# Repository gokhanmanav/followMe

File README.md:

# followMe

This application was developed for special education students.

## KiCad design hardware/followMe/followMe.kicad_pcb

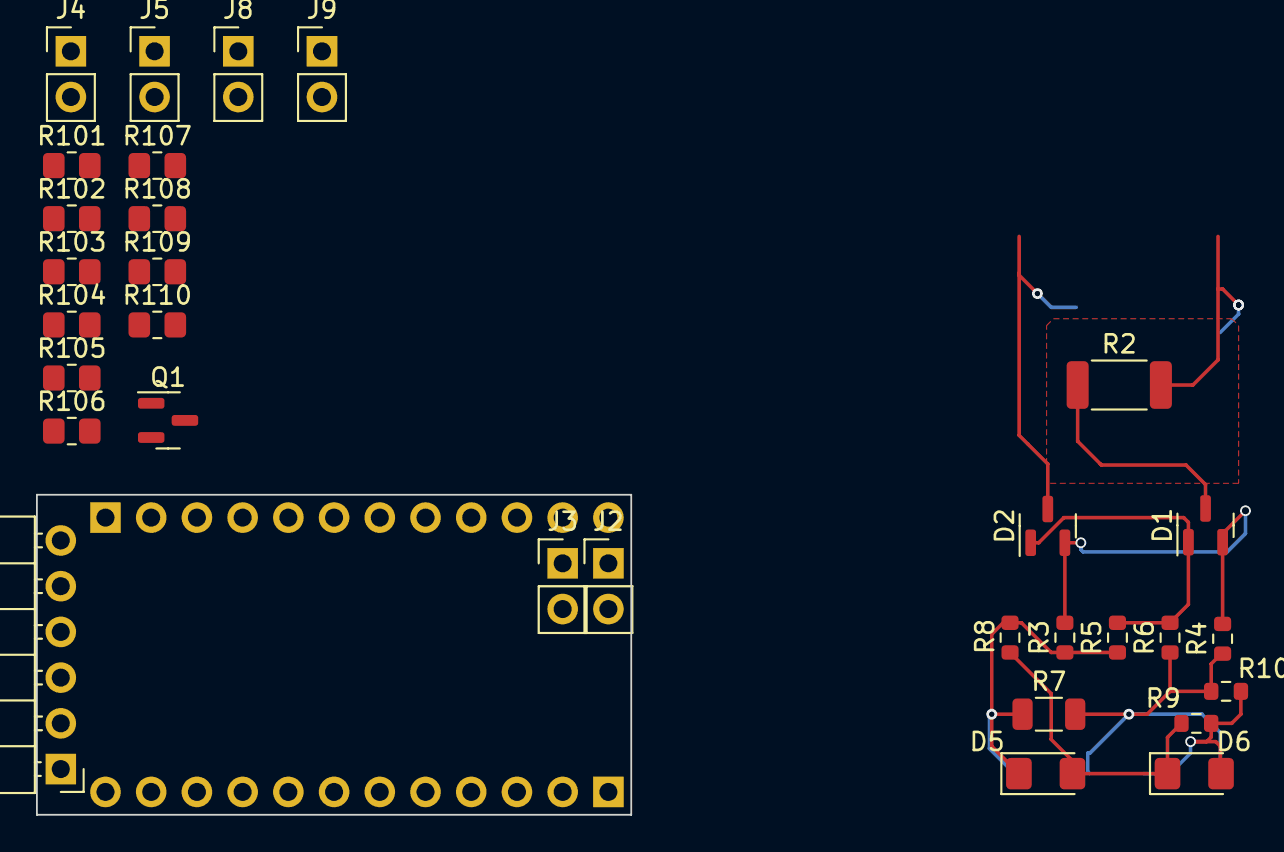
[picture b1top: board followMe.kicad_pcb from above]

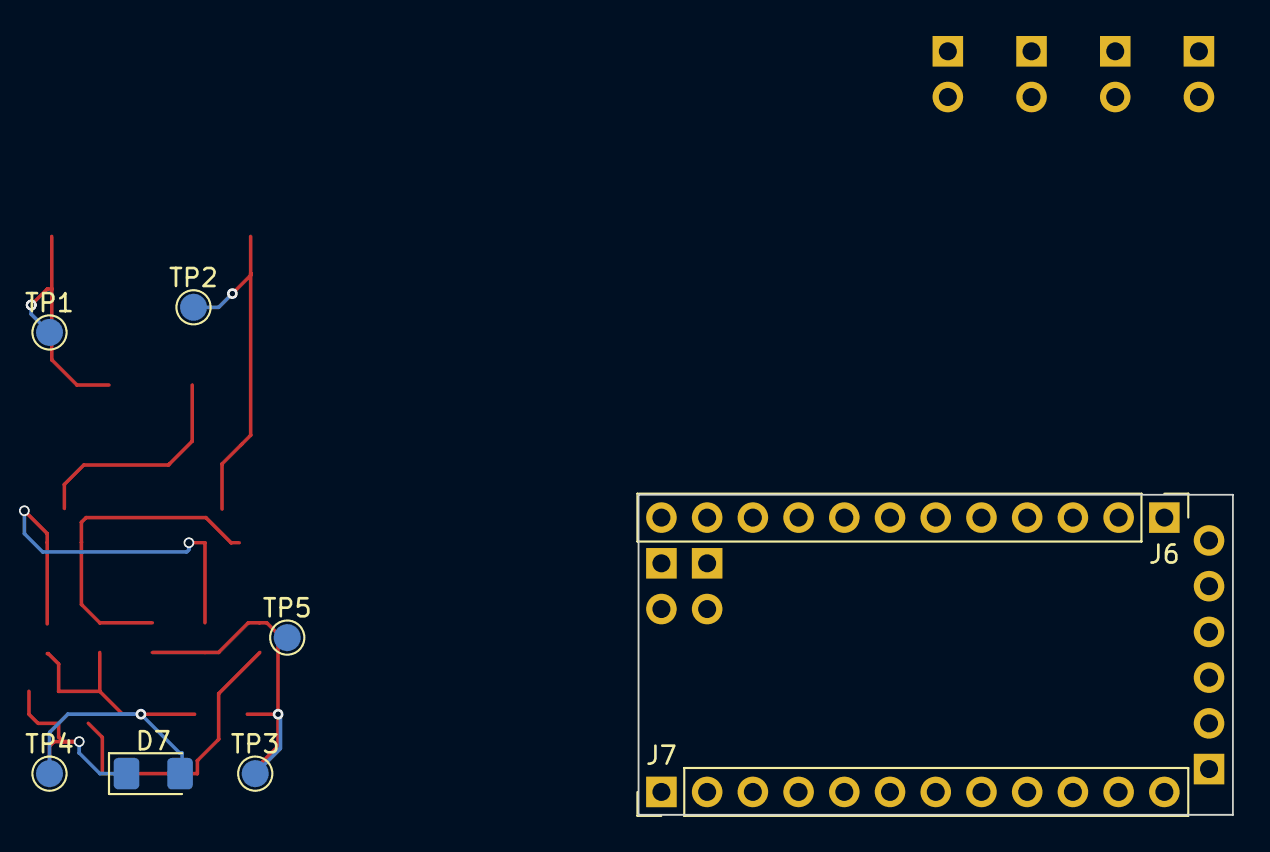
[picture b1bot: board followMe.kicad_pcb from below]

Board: 2 copper layers, 33.0 x 17.8 mm, 39 parts (8 on the bottom side), 26 nets.

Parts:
D1, D2: BAV99; SOT-23
D5, D6, D7: LED; LED_1206_3216Metric_Pad1.42x1.75mm_HandSolder
J1: FTDI; PinHeader_1x06_P2.54mm_Horizontal
J2: I2C; PinHeader_1x02_P2.54mm_Vertical
J3: Analog; PinHeader_1x02_P2.54mm_Vertical
J4: Vi+; PinHeader_1x02_P2.54mm_Vertical
J5: Vi-; PinHeader_1x02_P2.54mm_Vertical
J6: Analog; PinHeader_1x12_P2.54mm_Vertical
J7: Digital; PinHeader_1x12_P2.54mm_Vertical
J8: Vo-; PinHeader_1x02_P2.54mm_Vertical
J9: Vo+; PinHeader_1x02_P2.54mm_Vertical
Q1: MMBT2222A; SOT-23
R2: 1k; R_2010_5025Metric
R3, R6, R8, R9, R10: NC; R_0603_1608Metric
R4, R5: R; R_0603_1608Metric
R7: 1k5; R_1206_3216Metric
R101, R102: R; R_0805_2012Metric_Pad1.20x1.40mm_HandSolder
R103, R104, R105, R106: 220; R_0805_2012Metric_Pad1.20x1.40mm_HandSolder
R107, R108, R109, R110: 4k7; R_0805_2012Metric_Pad1.20x1.40mm_HandSolder
TP1, TP2, TP3, TP4, TP5: TestPoint; TestPoint_Pad_D1.5mm

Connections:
/*D3: J7.7, R104.1
/*D5: J7.5, R106.1
/*D6: J7.4, R102.1
/A0: J6.8, R107.2
/A1: J6.7, R108.2
/A2: J6.6, R109.2
/A3: J6.5, R110.2
/D2: J7.8, R103.1
/D4: J7.6, R105.1
/RX: J1.4, J7.11
/TX: J1.5, J7.12
/schineder button led circuit/Fill: D1.3 (K), R2.1, TP5.1
/schineder button led circuit/Vin1: D2.3 (K), TP2.1
/schineder button led circuit/Vin2: R2.2, TP1.1
/~RESET: J6.3, J7.10
GND: J1.1, J1.2, J6.2, J7.9, J8.1, J8.2, Q1.2 (E)
unnamed: J4.1, J4.2
unnamed: J5.1, J5.2
unnamed: D1.2 (A), D2.2 (A), R3.2, R4.2
unnamed: D1.1 (K), D2.1 (K), R5.2, R6.2
unnamed: D5.2 (A), D6.1 (K), R8.2, R9.1
unnamed: D5.1 (K), R3.1, R5.1, R7.1, R8.1, TP3.1
unnamed: D6.2 (A), D7.1 (K), R9.2, R10.2
unnamed: D7.2 (A), R4.1, R6.1, R7.2, R10.1, TP4.1
unnamed: Q1.1 (B), R102.2
VCC: J1.3, J6.4, J9.1, J9.2, R101.1, R107.1, R108.1, R109.1, R110.1

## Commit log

2024-02-08 firmware led fonksiyonları eklendi
2024-02-08 Version 1.0
2024-02-08 README.md eklendi
2024-02-17 Donanım
    Devre bağlantı şeması çizildi
2024-02-25 version 1.00
    First Versiyon
2024-02-27 V1.00
    ilk versiyon
2024-03-07 GLCD ekran eklendi
    Grafik LCD Ekran eklendi
2024-03-07 Revert "GLCD ekran eklendi"
    This reverts commit 4725419bf9b5e84ee3984d31ef229cf3f0ee9c22.
2024-03-07 v1.01
    Grafik LCD Ekran Eklendi
